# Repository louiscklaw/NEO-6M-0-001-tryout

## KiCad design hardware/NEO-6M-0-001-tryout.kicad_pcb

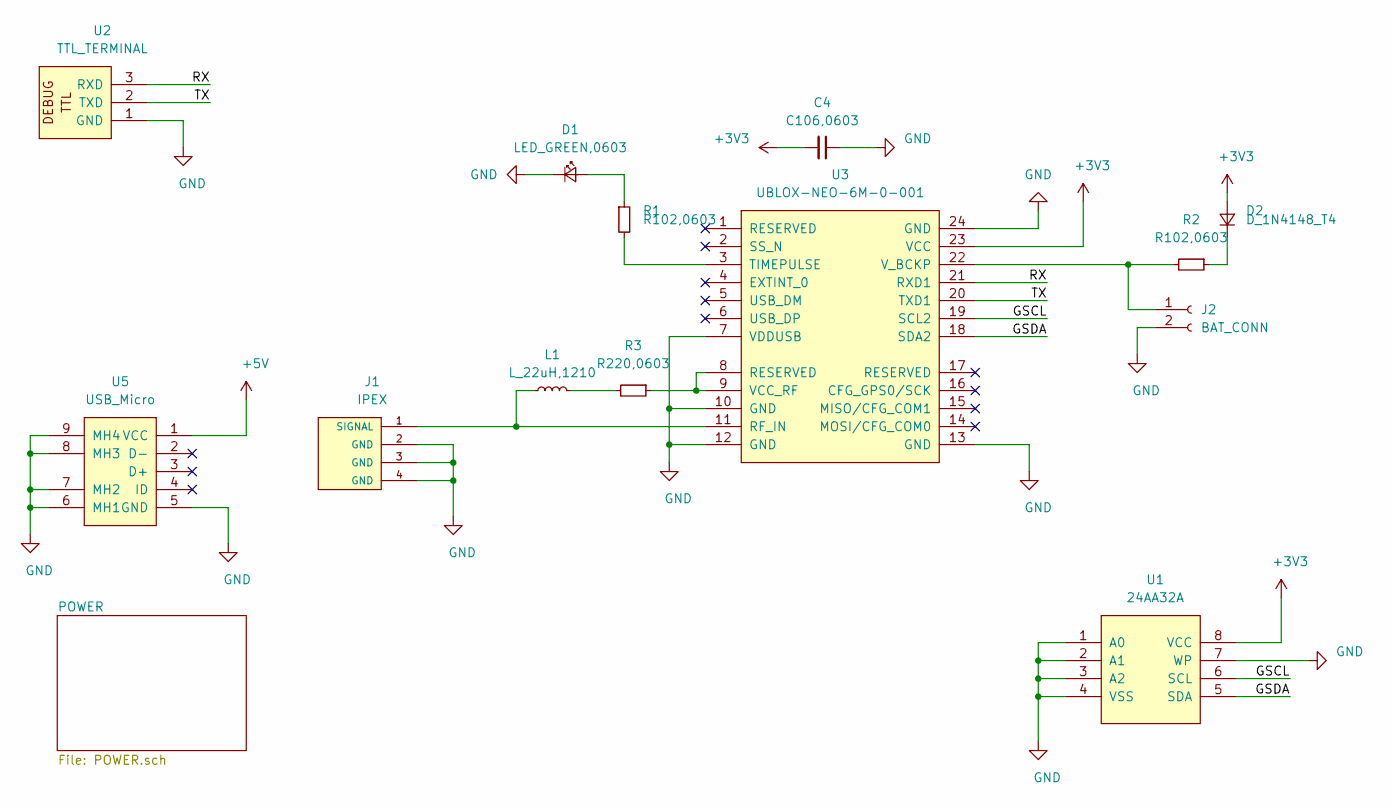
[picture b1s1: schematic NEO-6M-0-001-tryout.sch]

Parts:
C4: C106,0603; C_0603_1608Metric_Pad1.05x0.95mm_HandSolder
D1: LED_GREEN,0603; LED_0603_1608Metric
D2: D_1N4148_T4; D_SOD-123
J1: IPEX
J2: BAT_CONN; PinHeader_1x02_P2.54mm_Vertical
L1: L_22uH,1210; L_1210_3225Metric_Pad1.42x2.65mm_HandSolder
R1, R2: R102,0603; R_0603_1608Metric_Pad1.05x0.95mm_HandSolder
R3: R220,0603; R_0603_1608Metric_Pad1.05x0.95mm_HandSolder
U1: 24AA32A
U2: TTL_TERMINAL; PinHeader_1x03_P1.27mm_Vertical
U3: UBLOX-NEO-6M-0-001
U5: USB_Micro; USB_Micro-B_Molex-105017-0001

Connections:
+3V3: C4.2, D2.2 (A), U1.8 (VCC), U3.23 (VCC); also elsewhere on the board
+5V: U5.1 (VCC); also elsewhere on the board
/GSCL: U1.6 (SCL), U3.19 (SCL2)
/GSDA: U1.5 (SDA), U3.18 (SDA2)
/RX: U2.3 (RXD), U3.21 (RXD1)
/TX: U2.2 (TXD), U3.20 (TXD1)
GND: C4.1, D1.1 (K), J1.2 (GND), J1.3 (GND), J1.4 (GND), J2.2, U1.1 (A0), U1.2 (A1), U1.3 (A2), U1.4 (VSS), U1.7 (WP), U2.1 (GND), U3.7 (VDDUSB), U3.10 (GND), U3.12 (GND), U3.13 (GND), U3.24 (GND), U5.5 (GND), U5.6 (MH1), U5.7 (MH2), U5.8 (MH3), U5.9 (MH4); also elsewhere on the board
unnamed: D1.2 (A), R1.1
unnamed: D2.1 (K), R2.1
unnamed: J1.1 (SIGNAL), L1.1, U3.11 (RF_IN)
unnamed: J2.1, R2.2, U3.22 (V_BCKP)
unnamed: L1.2, R3.2
unnamed: R1.2, U3.3 (TIMEPULSE)
unnamed: R3.1, U3.8 (RESERVED), U3.9 (VCC_RF)

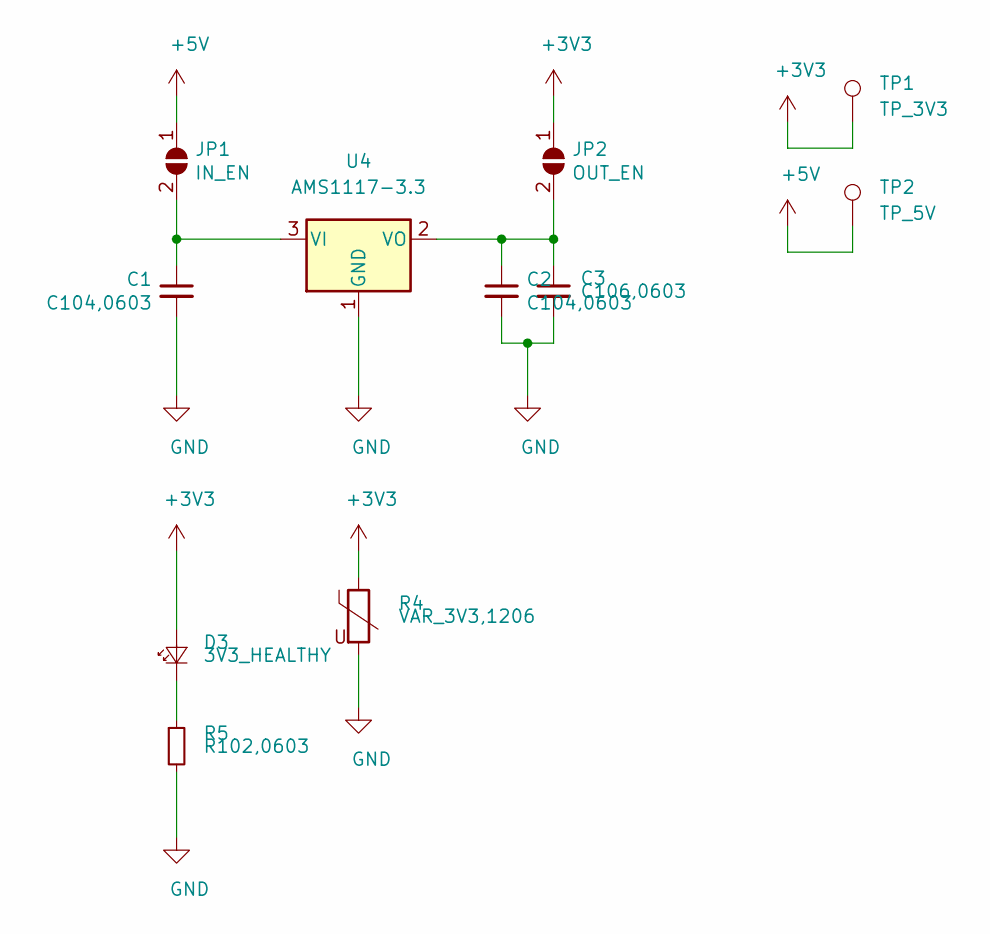
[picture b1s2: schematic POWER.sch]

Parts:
C1, C2: C104,0603; C_0603_1608Metric_Pad1.05x0.95mm_HandSolder
C3: C106,0603; C_0603_1608Metric_Pad1.05x0.95mm_HandSolder
D3: 3V3_HEALTHY; LED_0603_1608Metric_Pad1.05x0.95mm_HandSolder
JP1: IN_EN; SolderJumper-2_P1.3mm_Open_RoundedPad1.0x1.5mm
JP2: OUT_EN; SolderJumper-2_P1.3mm_Open_RoundedPad1.0x1.5mm
R4: VAR_3V3,1206; VAR_1206
R5: R102,0603; R_0603_1608Metric_Pad1.05x0.95mm_HandSolder
TP1: TP_3V3; Pin_D1.0mm_L10.0mm
TP2: TP_5V; Pin_D1.0mm_L10.0mm
U4: AMS1117-3.3; AMS1117_SOT-223

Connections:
+3V3: D3.2 (A), JP2.1 (A), R4.1, TP1.1; also elsewhere on the board
+5V: JP1.1 (A), TP2.1; also elsewhere on the board
GND: C1.2, C2.2, C3.2, R4.2, R5.2, U4.1 (GND); also elsewhere on the board
unnamed: C1.1, JP1.2 (B), U4.3 (VI)
unnamed: C2.1, C3.1, JP2.2 (B), U4.2 (VO)
unnamed: D3.1 (K), R5.1

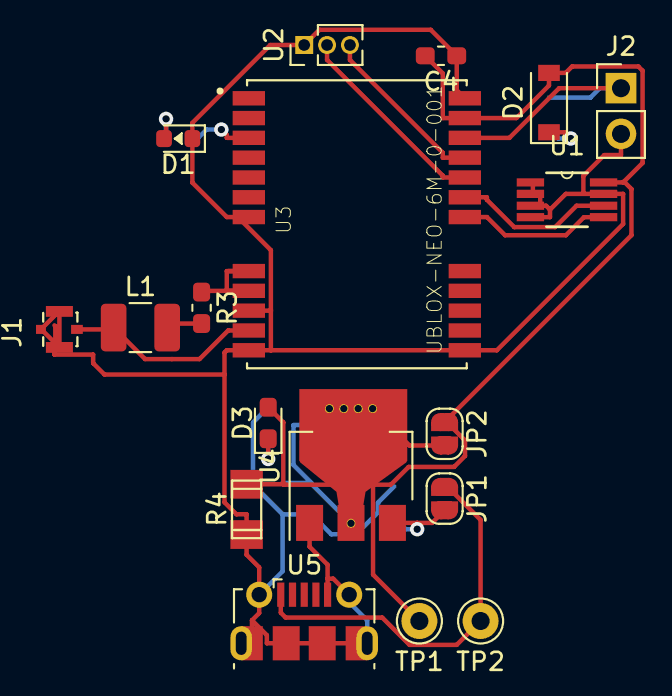
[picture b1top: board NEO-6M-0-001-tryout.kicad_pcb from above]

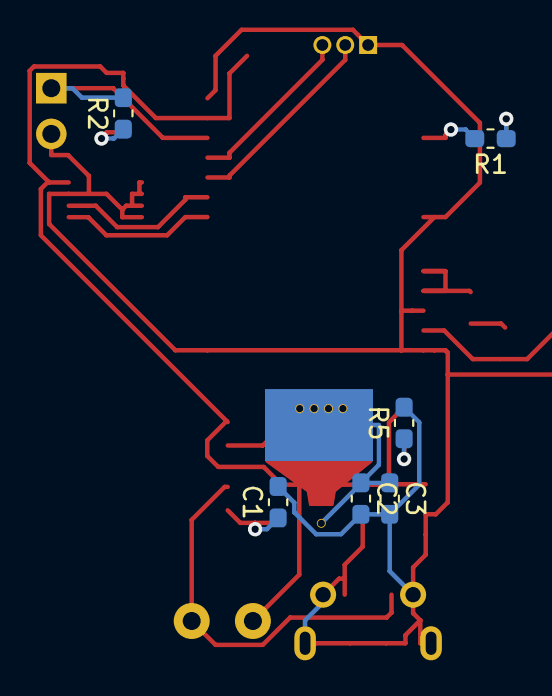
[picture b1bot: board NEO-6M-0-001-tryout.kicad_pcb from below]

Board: 2 copper layers, 24 parts (6 on the bottom side), 17 nets.

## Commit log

2019-06-25 update,
2020-05-06 ci: init travis build config,
2020-05-06 ci: init travis token,
